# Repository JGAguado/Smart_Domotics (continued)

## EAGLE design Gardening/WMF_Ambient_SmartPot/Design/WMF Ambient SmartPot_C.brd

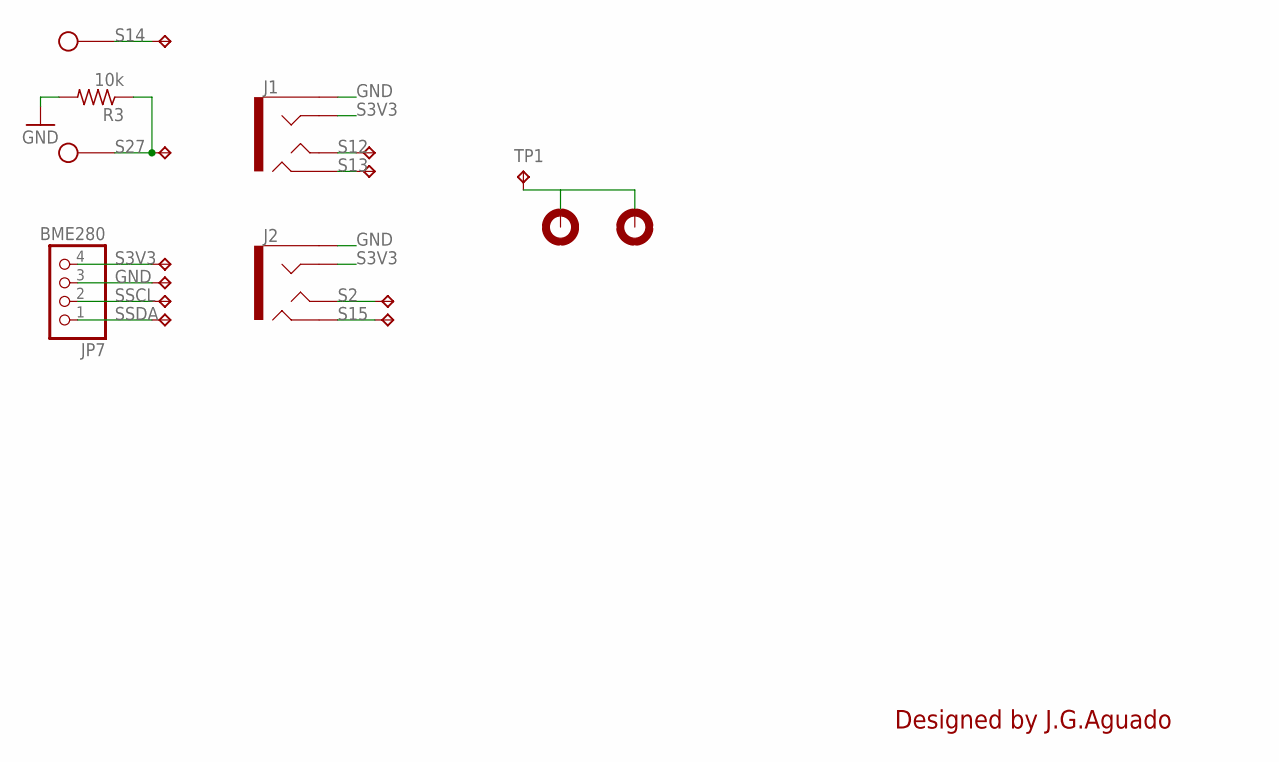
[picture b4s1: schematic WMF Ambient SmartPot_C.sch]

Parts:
H1, H2: MOUNT-PAD-ROUND2.8; 2,8-PAD
J1, J2: AUDIO_JACK_TRRSSMD_RA; AUDIO_JACK_3.5MM_TRRS_SMD_RA
JP7: BME280; 1X04
R3: 10k; 1206
TP1, TP6, TP7, TP8, TP9, TP12, TP16, TP17, TP20, TP21, TP23: TPTP15SQ; TP15SQ
U$2, U$3: OVAL_3MM_HOLE; OVAL_HOLE

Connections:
GND: J1.EARTH, J2.EARTH, JP7.3, R3.2, TP7.TP
S2: J2.TIP, TP20.TP
S3V3: J1.RING1, J2.RING1, JP7.4, TP6.TP
S12: J1.TIP, TP16.TP
S13: J1.RING2, TP17.TP
S14: TP12.TP, U$2.P$2
S15: J2.RING2, TP21.TP
S27: R3.1, TP23.TP, U$3.P$2
SSCL: JP7.2, TP8.TP
SSDA: JP7.1, TP9.TP
TOUCH: H1.B2,8, H2.B2,8, TP1.TP

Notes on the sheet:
Designed by J.G.Aguado

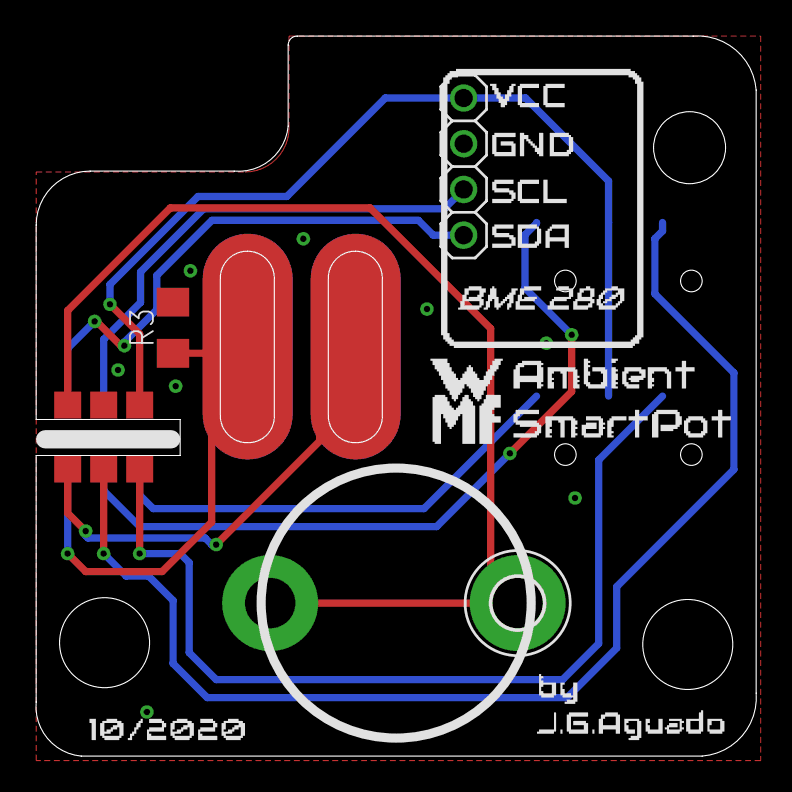
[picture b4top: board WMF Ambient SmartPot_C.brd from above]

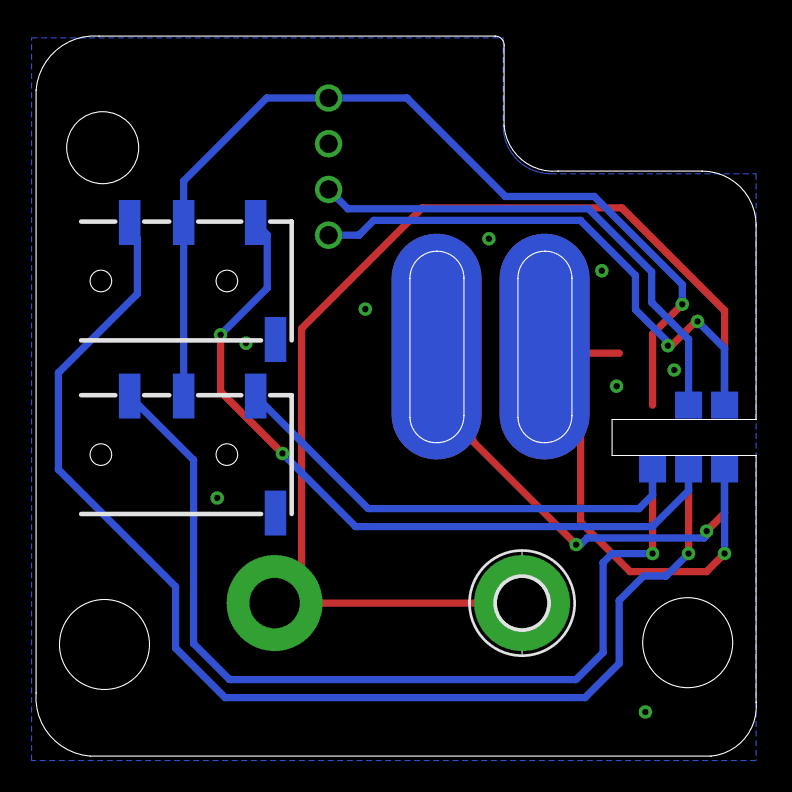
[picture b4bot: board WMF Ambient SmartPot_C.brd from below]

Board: 2 copper layers, 40.0 x 40.0 mm, 19 parts (8 on the bottom side), 11 nets.

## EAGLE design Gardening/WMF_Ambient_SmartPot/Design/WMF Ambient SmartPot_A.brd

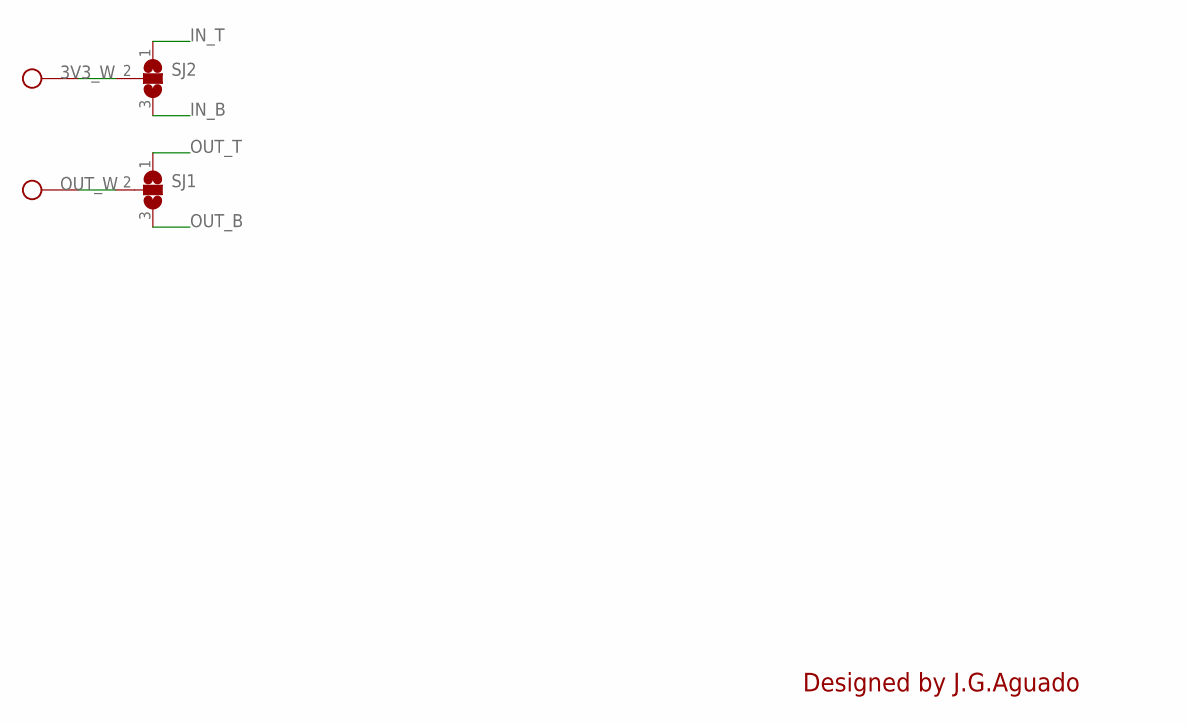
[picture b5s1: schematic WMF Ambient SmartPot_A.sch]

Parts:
SJ1, SJ2: SJ2W; SJ_2
U$4, U$5: OVAL_3MM_HOLE; OVAL_HOLE

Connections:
3V3_W: SJ2.2, U$4.P$2
IN_B: SJ2.3
IN_T: SJ2.1
OUT_B: SJ1.3
OUT_T: SJ1.1
OUT_W: SJ1.2, U$5.P$2

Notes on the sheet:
Designed by J.G.Aguado

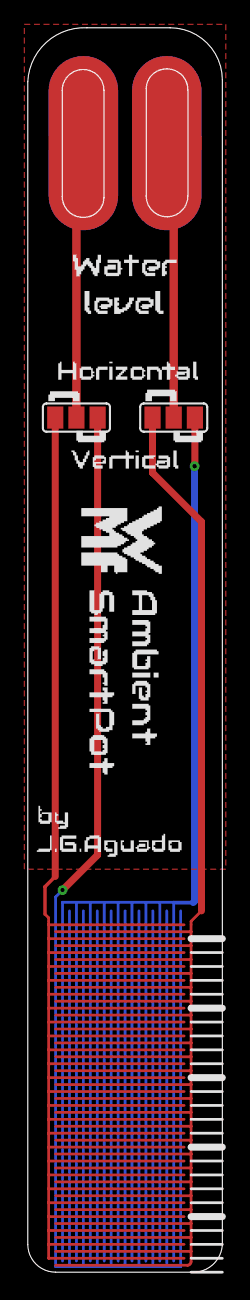
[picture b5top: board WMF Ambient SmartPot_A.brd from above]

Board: 2 copper layers, 14.0 x 89.6 mm, 4 parts (0 on the bottom side), 2 nets.

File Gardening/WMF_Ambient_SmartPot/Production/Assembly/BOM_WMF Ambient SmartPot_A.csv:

"Part";"Value";"Device";"Package";"Description";"POPULARITY";
"SJ1";"";"SJ2W";"SJ_2";"SMD solder JUMPER";"7";
"SJ2";"";"SJ2W";"SJ_2";"SMD solder JUMPER";"7";
"U$4";"OVAL_3MM_HOLE";"OVAL_3MM_HOLE";"OVAL_HOLE";"";"";
"U$5";"OVAL_3MM_HOLE";"OVAL_3MM_HOLE";"OVAL_HOLE";"";"";

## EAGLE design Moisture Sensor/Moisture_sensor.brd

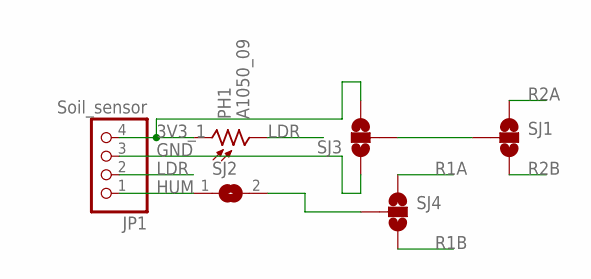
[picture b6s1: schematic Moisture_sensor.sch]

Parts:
JP1: Soil_sensor; 1X04
PH1: A1050_09; T0-46-A10XX
SJ1, SJ3, SJ4: SOLDERJUMPER_2WAYS; SJ_3
SJ2: SJ

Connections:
3V3_1: JP1.4, PH1.1, SJ3.3
GND: JP1.3, SJ3.1
HUM: JP1.1, SJ2.1
LDR: JP1.2, PH1.2
unnamed: SJ2.2, SJ4.2
unnamed: SJ1.2, SJ3.2
R1A: SJ4.1
R1B: SJ4.3
R2A: SJ1.1
R2B: SJ1.3

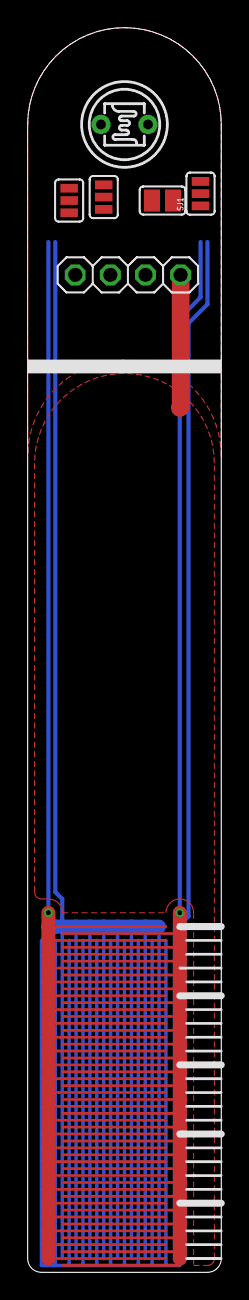
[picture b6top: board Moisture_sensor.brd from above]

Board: 2 copper layers, 14.0 x 90.0 mm, 6 parts (0 on the bottom side), 6 nets.

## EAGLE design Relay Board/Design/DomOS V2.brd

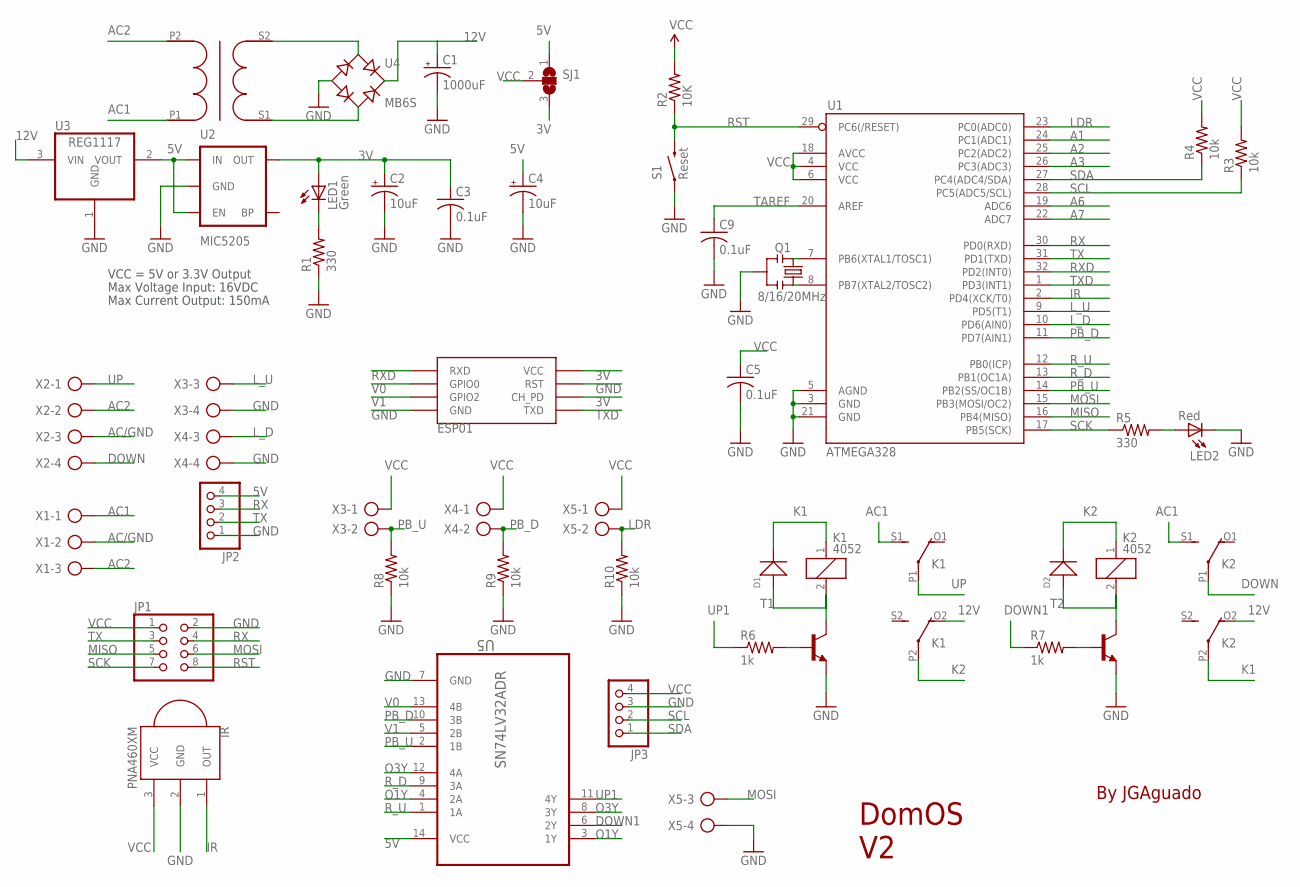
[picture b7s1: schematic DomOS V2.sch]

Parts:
C1: 1000uF; 140CLH-0810
C2, C4: 10uF; EIA3216
C3, C5, C9: 0.1uF; C1206
D1, D2: SMD-DIODE-SWITCHING-75V-150MA(D1206); LED-1206
ESP01: ESP01
IR: PNA460XM
JP1: PINHD-2X4; 2X04
JP2, JP3: PINHD-1X4; 1X04
K1, K2: 4052; F4052
LED1: Green; 1206
LED2: Red; 1206
Q1: 8/16/20MHz; RESONATOR-SMD
R1, R5: 330; R1206
R2: 10K; R1206
R3, R4, R8, R9, R10: 10k; R1206
R6, R7: 1k; R1206
S1: Reset; TACTILE_SWITCH_TALL
SJ1: SJ2W; SJ_2
T1, T2: BC817-16-NPN-SOT23-BEC; SOT23-BEC
U1: ATMEGA328; TQFP32-08
U2: MIC5205; SOT23-5
U3: REG1117; SOT223
U4: MB6S; SOIC-4
U5: SN74LV32ADR; SOIC127P600X175-14N
U$1: TRANSFORMADOR_PE3010-M
X1: AK500/3
X2, X3, X4, X5: AK500/4

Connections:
3V: C2.A (+), C3.1, ESP01.CH_PD, ESP01.VCC, LED1.A, SJ1.3, U2.5 (OUT)
5V: C4.A (+), JP2.4, SJ1.1, U2.1 (IN), U2.3 (EN), U3.2 (VOUT), U5.14 (VCC)
12V: C1.+, K1.O2 (O), K2.O2 (O), U3.3 (VIN), U4.+
A1: U1.24 (PC1(ADC1))
A2: U1.25 (PC2(ADC2))
A3: U1.26 (PC3(ADC3))
A6: U1.19 (ADC6)
A7: U1.22 (ADC7)
AC1: K1.S1 (S), K2.S1 (S), U$1.P1, X1.1
AC2: U$1.P2, X1.3, X2.2
AC/GND: X1.2, X2.3
DOWN: K2.P1, X2.4
DOWN1: R7.1, U5.6 (2Y)
GND: C1.-, C2.C (-), C3.2, C4.C (-), C5.2, C9.2, ESP01.GND, ESP01.RST, IR.2 (GND), JP1.2, JP2.1, JP3.3, LED2.C, Q1.2, R1.1, R8.1, R9.1, R10.1, S1.A2 (1), T1.E, T2.E, U1.3 (GND), U1.5 (AGND), U1.21 (GND), U2.2 (GND), U3.1 (GND), U4.-, U5.7 (GND), X3.4, X4.4, X5.4
IR: IR.1 (OUT), U1.2 (PD4(XCK/T0))
K1: D1.-, K1.1, K2.P2
K2: D2.-, K1.P2, K2.1
LDR: R10.2, U1.23 (PC0(ADC0)), X5.2
L_D: U1.10 (PD6(AIN0)), X4.3
L_U: U1.9 (PD5(T1)), X3.3
MISO: JP1.5, U1.16 (PB4(MISO))
MOSI: JP1.6, U1.15 (PB3(MOSI/OC2)), X5.3
unnamed: U4.~1 (AC1), U$1.S2
unnamed: U4.~2 (AC2), U$1.S1
unnamed: D1.+, K1.2, T1.C
unnamed: Q1.3, U1.8 (PB7(XTAL2/TOSC2))
unnamed: Q1.1, U1.7 (PB6(XTAL1/TOSC1))
unnamed: LED2.A, R5.2
unnamed: LED1.C, R1.2
unnamed: R6.2, T1.B
unnamed: D2.+, K2.2, T2.C
unnamed: R7.2, T2.B
O1Y: U5.3 (1Y), U5.4 (2A)
O3Y: U5.8 (3Y), U5.12 (4A)
PB_D: R9.2, U1.11 (PD7(AIN1)), U5.10 (3B), X4.2
PB_U: R8.2, U1.14 (PB2(SS/OC1B)), U5.2 (1B), X3.2
RST: JP1.8, R2.1, S1.B2 (2), U1.29 (PC6(/RESET))
RX: JP1.4, JP2.3, U1.30 (PD0(RXD))
RXD: ESP01.RX (RXD), U1.32 (PD2(INT0))
R_D: U1.13 (PB1(OC1A)), U5.9 (3A)
R_U: U1.12 (PB0(ICP)), U5.1 (1A)
SCK: JP1.7, R5.1, U1.17 (PB5(SCK))
SCL: JP3.2, R3.1, U1.28 (PC5(ADC5/SCL))
SDA: JP3.1, R4.1, U1.27 (PC4(ADC4/SDA))
TAREF: C9.1, U1.20 (AREF)
TX: JP1.3, JP2.2, U1.31 (PD1(TXD))
TXD: ESP01.TX (TXD), U1.1 (PD3(INT1))
UP: K1.P1, X2.1
UP1: R6.1, U5.11 (4Y)
V0: ESP01.GPIO0, U5.13 (4B)
V1: ESP01.GPIO2, U5.5 (2B)
VCC: C5.1, IR.3 (VCC), JP1.1, JP3.4, R2.2, R3.2, R4.2, SJ1.2, U1.4 (VCC), U1.6 (VCC), U1.18 (AVCC), X3.1, X4.1, X5.1

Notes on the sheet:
Max Voltage Input: 16VDC
Max Current Output: 150mA
VCC = 5V or 3.3V Output
By JGAguado
DomOS V2

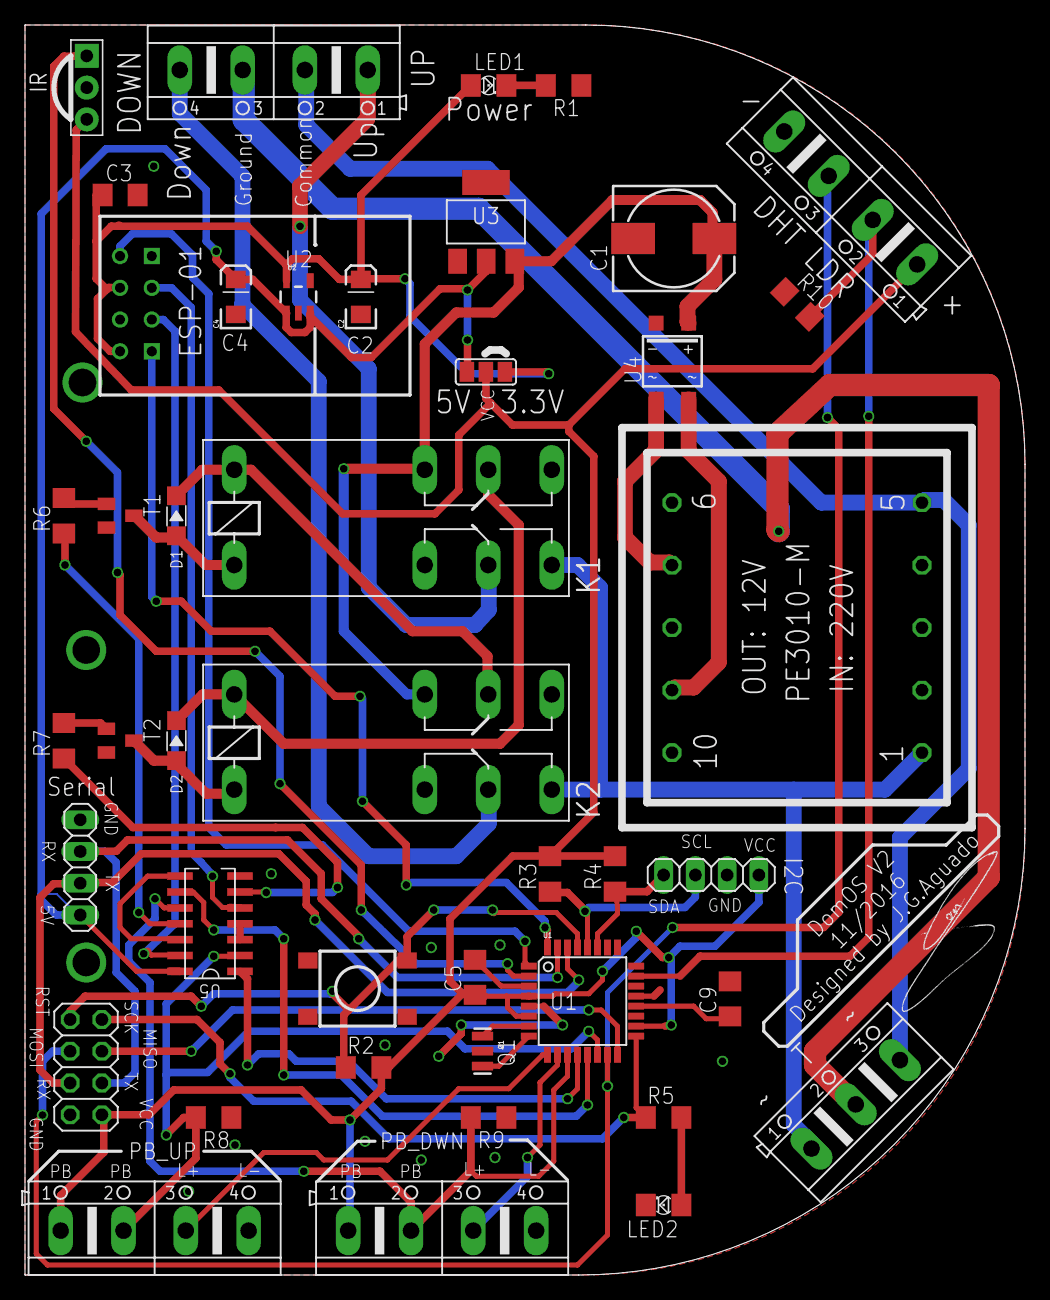
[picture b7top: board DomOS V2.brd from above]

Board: 2 copper layers, 80.0 x 100.0 mm, 43 parts (0 on the bottom side), 47 nets.

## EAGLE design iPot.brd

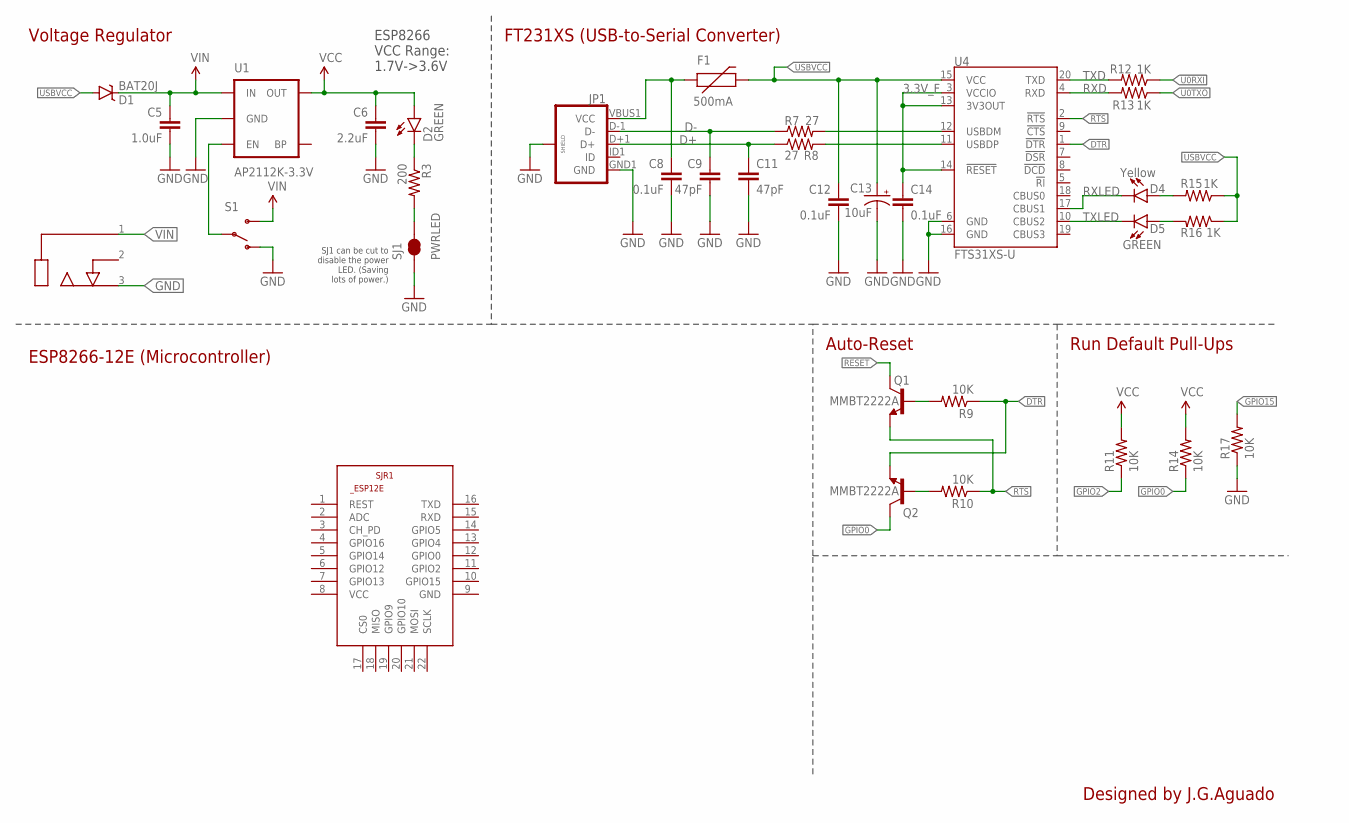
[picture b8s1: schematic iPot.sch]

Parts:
C5: 1.0uF; 0805
C6: 2.2uF; 0603-CAP
C8, C12, C14: 0.1uF; 0603-CAP
C9, C11: 47pF; 0603-CAP
C13: 10uF; EIA3216
D1: BAT20J; SOD-323
D2, D5: GREEN; LED-0603
D4: Yellow; LED-0603
F1: 500mA; PTC-1206
JP1: USB_MICROB_PLUGCONN-11752; USB-B-MICRO-SMD_V03
JP2: DC_JACK_1.3
Q1, Q2: MMBT2222A; SOT23-3
R3: 200; 0603-RES
R7, R8: 27; 0603-RES
R9, R10, R11, R14, R17: 10K; 0603-RES
R12, R13, R15, R16: 1K; 0603-RES
S1: SWITCH-SPDT-SMD-A; SWITCH-SPST-SMD-A
SJ1: PWRLED; PAD-JUMPER-2-NC_BY_TRACE_YES_SILK
SJR1: ESP8266-12EESP12E; ESP8266-ESP12E
U1: AP2112K-3.3V; SOT23-5
U4: FTS31XS-U; SSOP20_L

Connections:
3.3V_F: C14.1, U4.3 (VCCIO), U4.13 (3V3OUT), U4.14 (!RESET)
D+: C11.1, JP1.D+1 (D+), R8.1
D-: C9.1, JP1.D-1 (D-), R7.1
DTR: Q2.2 (E), R9.1, U4.1 (!DTR)
GND: C5.2, C6.2, C8.2, C9.2, C11.2, C12.2, C13.C (-), C14.2, JP1.GND1 (GND), JP1.SHIELD1 (SHIELD), JP1.SHIELD2 (SHIELD), JP1.SHIELD3 (SHIELD), JP2.3, R17.1, S1.1 (O), SJ1.1, U1.2 (GND), U4.6 (GND), U4.16 (GND)
GPIO0: Q2.3 (C), R14.1
GPIO2: R11.1
GPIO15: R17.2
unnamed: R7.2, U4.12 (USBDM)
unnamed: R3.2, SJ1.2
unnamed: Q1.1 (B), R9.2
unnamed: R8.2, U4.11 (USBDP)
unnamed: D5.A, R16.2
unnamed: D4.A, R15.2
unnamed: D2.C, R3.1
unnamed: Q2.1 (B), R10.2
unnamed: S1.2, U1.3 (EN)
RESET: Q1.3 (C)
RTS: Q1.2 (E), R10.1, U4.2 (!RTS)
RXD: R13.2, U4.4 (RXD)
RXLED: D4.C, U4.17 (CBUS1)
TXD: R12.2, U4.20 (TXD)
TXLED: D5.C, U4.10 (CBUS2)
U0RXI: R12.1
U0TXO: R13.1
USBVCC: C12.1, C13.A (+), D1.A, F1.2, R15.1, R16.1, U4.15 (VCC)
VCC: C6.1, D2.A, R11.2, R14.2, U1.5 (OUT)
VIN: C5.1, D1.C, JP2.1, S1.3 (S), U1.1 (IN)
VUSB: C8.1, F1.1, JP1.VBUS1 (VCC)

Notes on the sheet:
ESP8266 VCC Range: 1.7V->3.6V
Voltage Regulator
FT231XS (USB-to-Serial Converter)
Auto-Reset
Run Default Pull-Ups
SJ1 can be cut to disable the power LED. (Saving lots of power.)
Designed by J.G.Aguado
ESP8266-12E (Microcontroller)

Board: 2 copper layers, 34 parts (0 on the bottom side), 24 nets, no tracks yet.

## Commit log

2019-05-23 Bugs fixing
2020-09-30 Updated with Schematics and Board layout
2020-10-01 Added Moisture Sensor and Relay Board folders with initial data (Relay board is directly the blinds controller)
2020-10-12 Updated Irrigation Controller
2020-10-12 Updated WMF SmartPot V1.0 with production files
2020-10-14 Updated Schematics and Board
2020-10-23 Irrigation controller with support for: * 220 VAC * 24 VAC * 9 VDC * 5 VDC * 3.3 VDC
2020-10-24 Addapted SCH and BRD to work with low-voltage on the outputs
2020-11-01 Domotics repository updated with ./Gardening/Smart_Garden and ./Gardening/WMF_Ambient_SmartPot Projects
2020-11-29 Updated Smart Garden Project docomentation
2020-12-07 Changed the panelized design to individual boards design
2020-12-07 Fixed Documentation/Schematic.pdf for Smart_Garden
2020-12-08 First commit to Smart Garden V1.1.0, changes apply mainly to schematics: * Relay 5V supply * Removed 220-24VAC transformator * Staged power supply regulation with 12V step * Push-buttons connection p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
2020-12-13 Updated Design files
2020-12-13 Updated Documentation and Silkscreen for V1.1
2020-12-13 Updated Production files ready to order for Smart-garden V1.1.0
2020-12-15 Updated Design files WMF Ambient SmartPot_B
2021-12-14 Added first commit of SmartPlant design, with the model 1 ready for production
2021-12-14 Fixed coomit for Smart_plant
2021-12-14 Fixed structure for Smart_Garden and WMF_Ambient_SmartPot board
2021-12-14 Added Smart Lights project
2021-12-14 Added Smart Power-meter project
2021-12-14 Change in the structure, updated README.md and added LICENSE and .gitignore
2021-12-21 Set theme jekyll-theme-cayman
2022-03-28 Added the Smart-bike submodule
2022-04-15 Updated Smart_Domotics repo with new structure
2022-04-15 Updated structure and README.md
2022-10-06 Added Smart_Alarm
2022-10-06 Update Smart_Domotics
2022-11-01 Updated subdirectories
2023-03-05 Updated Smart_Garden & Smart_Lights
2023-03-05 Added Smart_Dashboard
